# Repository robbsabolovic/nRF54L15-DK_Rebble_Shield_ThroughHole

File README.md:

# nRF54L15-DK Rebble Shield Through Hole Headers

---
KiCAD PCB template with through hole headers to nRF54L15-DK.  
Intended to support Rebble contestants on [Hackster.io](https://Hackster.io)

This KiCAD Template simplifies initial setup for creating an nRF54L15-DK Shield Through Hole PCB designs.<br>
To begin, clone this repository to your KICAD_USER_TEMPLATE_DIR as found under "Preferences > Configure Paths..."<br>
Next, use "File > New Project from Template..." or "Ctrl+T" and select "User Templates." Select the template and begin!

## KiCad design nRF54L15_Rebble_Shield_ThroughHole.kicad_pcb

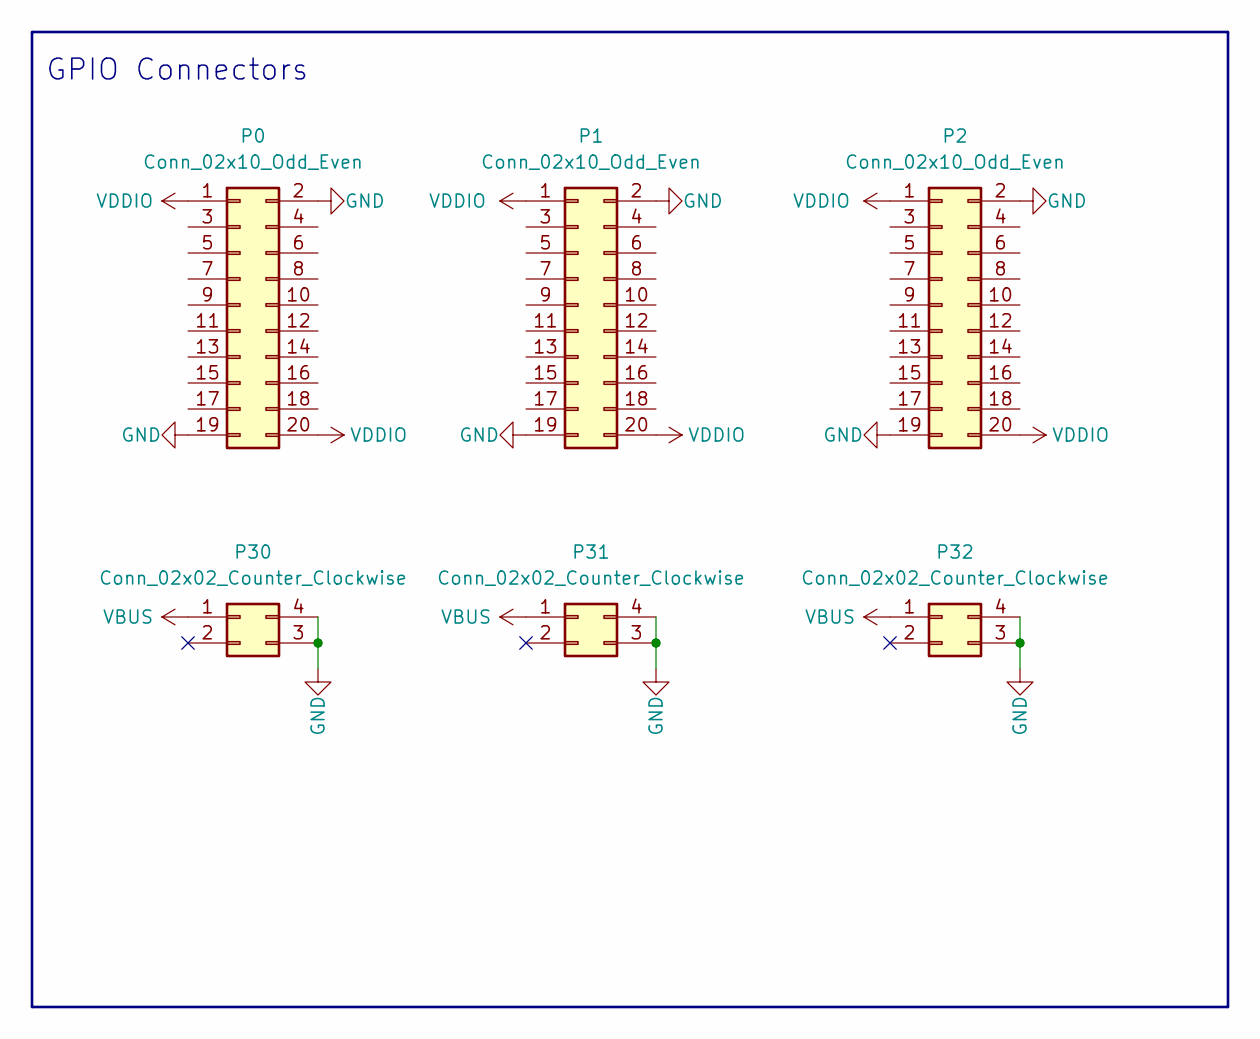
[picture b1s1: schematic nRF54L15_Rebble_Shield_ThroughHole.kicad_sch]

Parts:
P0, P1, P2: Conn_02x10_Odd_Even; PinHeader_2x10_P2.54mm_Vertical
P30, P31, P32: Conn_02x02_Counter_Clockwise; PinHeader_2x02_P2.54mm_Vertical

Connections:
GND: P0.2, P0.19, P1.2, P1.19, P2.2, P2.19, P30.3, P30.4, P31.3, P31.4, P32.3, P32.4
VBUS: P30.1, P31.1, P32.1
VDDIO: P0.1, P0.20, P1.1, P1.20, P2.1, P2.20

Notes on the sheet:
GPIO Connectors

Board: 4 copper layers, 8 parts (1 on the bottom side), 3 nets, no tracks yet.

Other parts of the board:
G**: Nordic Logo; NORDIC_LOGO_LYING
G**#2: Nordic Logo; NORDIC_LOGO_LYING

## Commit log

2025-02-25 nRF54L15_Rebble_Shield_ThroughHole initial release
    KiCad 9 PCB Template for an nRF54L15-DK shield (Through hole version)
